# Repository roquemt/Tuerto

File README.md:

# Tuerto
Obstacle avoider robot controled with a FSM 

Top view

Bottom view

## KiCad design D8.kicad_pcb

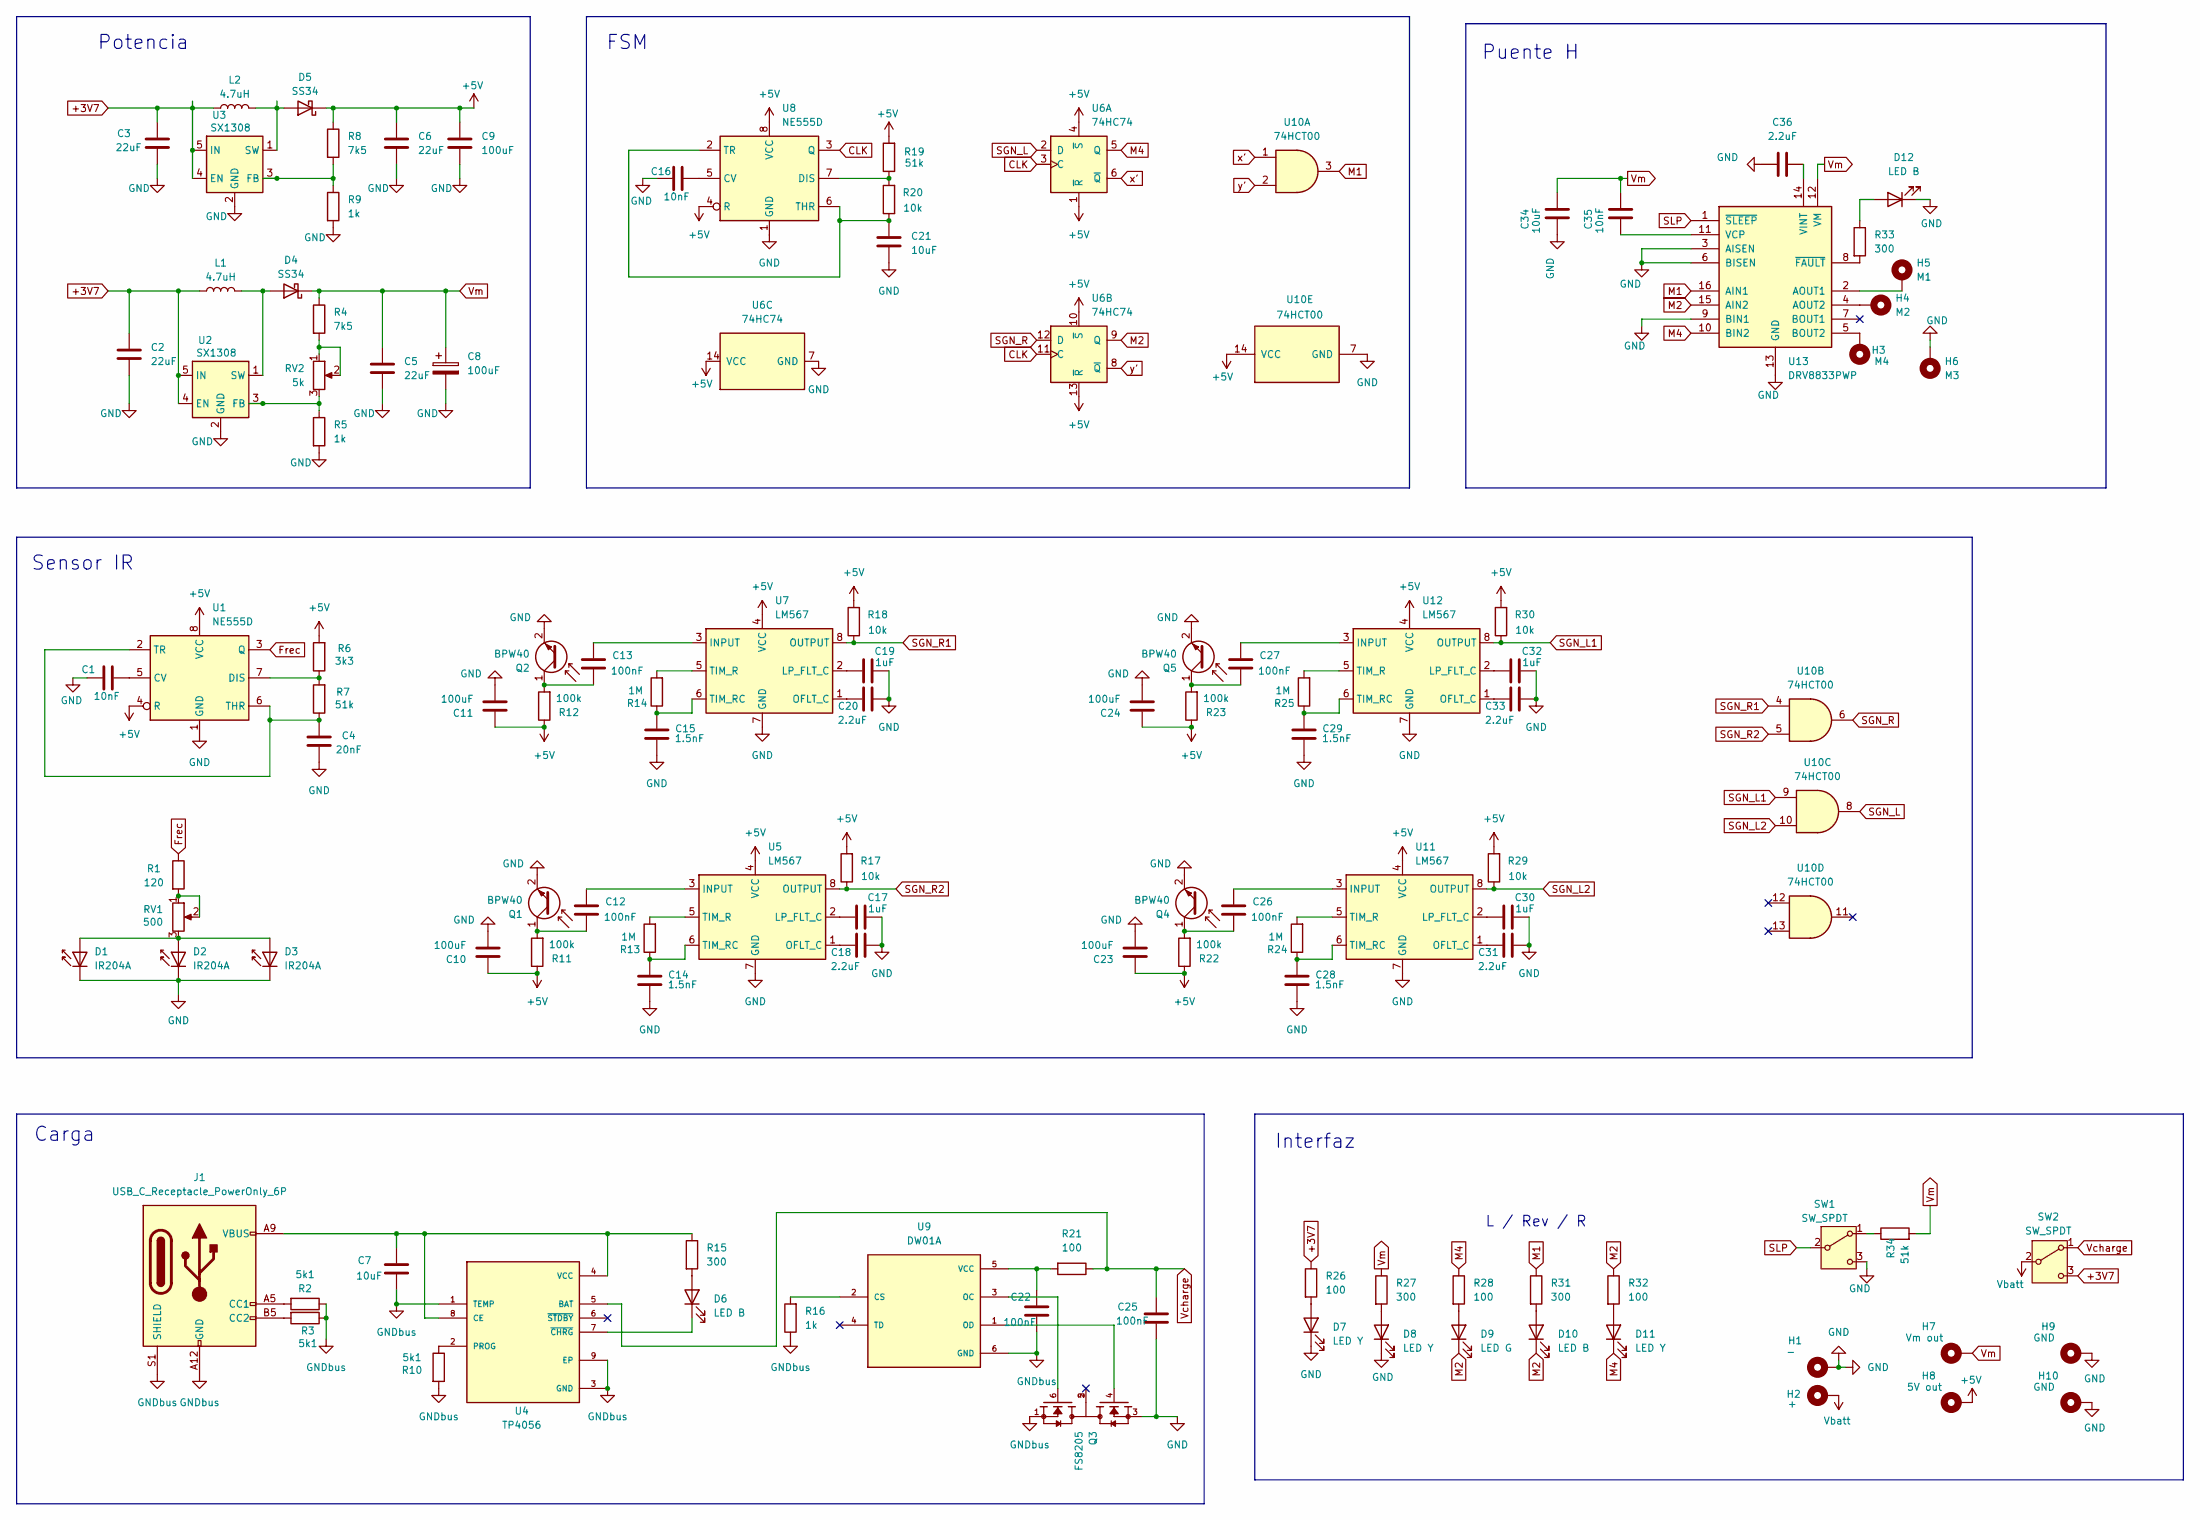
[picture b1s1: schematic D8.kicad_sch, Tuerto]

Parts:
C1, C16, C35: 10nF; C_0603_1608Metric
C2, C3, C5, C6: 22uF; C_0805_2012Metric
C4: 20nF; C_0603_1608Metric
C7, C21, C34: 10uF; C_0603_1608Metric
C8: 100uF; CP_EIA-6032-20_AVX-F_Pad2.25x2.35mm_HandSolder; Manufacturer Part Number TAJD107K016RNJ
C9, C10, C11, C23, C24: 100uF; C_1206_3216Metric
C12, C13, C22, C25, C26, C27: 100nF; C_0603_1608Metric
C14, C15, C28, C29: 1.5nF; C_0603_1608Metric
C17, C19, C30, C32: 1uF; C_0603_1608Metric
C18, C20, C31, C33, C36: 2.2uF; C_0603_1608Metric
D1, D2, D3: IR204A; LED_D3.0mm_IRBlack
D4, D5: SS34; D_SMA; Manufacturer Part Number SS34
D6, D10, D12: LED B; LED_1206_3216Metric
D7, D8, D11: LED Y; LED_1206_3216Metric
D9: LED G; LED_1206_3216Metric
H1: -; SolderWirePad_1x01_SMD_1x2mm
H2: +; SolderWirePad_1x01_SMD_1x2mm
H3: M4; MountingHole_2.2mm_M2_Pad
H4: M2; MountingHole_2.2mm_M2_Pad
H5: M1; MountingHole_2.2mm_M2_Pad
H6: M3; MountingHole_2.2mm_M2_Pad
H7: Vm out; SolderWirePad_1x01_SMD_1x2mm
H8: 5V out; SolderWirePad_1x01_SMD_1x2mm
H9, H10: GND; SolderWirePad_1x01_SMD_1x2mm
J1: USB_C_Receptacle_PowerOnly_6P; USB_C_Receptacle_GCT_USB4125-xx-x-0190_6P_TopMnt_Horizontal
L1, L2: 4.7uH; L_Changjiang_FNR4018S; Manufacturer Part Number FNR4018S4R7MT
Q1, Q2, Q4, Q5: BPW40; LED_D5.0mm_Clear
Q3: FS8205; SOT-23-6; Manufacturer Part Number FS8205A
R1: 120; R_1206_3216Metric
R2, R3, R10: 5k1; R_0603_1608Metric
R4: 7k5; R_0603_1608Metric
R5, R9, R16: 1k; R_0603_1608Metric
R6: 3k3; R_0603_1608Metric
R7, R19, R34: 51k; R_0603_1608Metric
R8: 7k5; R_0603_1608Metric; Manufacturer Part Number 0603WAF7501T5E
R11, R12, R22, R23: 100k; R_0603_1608Metric
R13, R14, R24, R25: 1M; R_0603_1608Metric
R15, R27, R31, R33: 300; R_1206_3216Metric
R17, R18, R20, R29, R30: 10k; R_0603_1608Metric
R21: 100; R_0603_1608Metric
R26, R28, R32: 100; R_1206_3216Metric
RV1: 500; Potentiometer_Bourns_TC33X_Vertical; Manufacturer Part Number TC33X-2-103E
RV2: 5k; Potentiometer_Bourns_TC33X_Vertical; Manufacturer Part Number TC33X-2-103E
SW1, SW2: SW_SPDT; SW_SPDT_PCM12; Manufacturer Part Number SK-3296S-01-L1
U1, U8: NE555D; SOIC-8_3.9x4.9mm_P1.27mm; Manufacturer Part Number NE555D
U2, U3: SX1308; SOT-23-6; Manufacturer Part Number SX1308
U4: TP4056; SOP-8-1EP_4.57x4.57mm_P1.27mm_EP4.57x4.45mm; Manufacturer Part Number TP4056
U5, U7, U11, U12: LM567; SOP-8_3.9x4.9mm_P1.27mm
U6: 74HC74; TSSOP-14_4.4x5mm_P0.65mm; Manufacturer Part Number SN74HCT74PWR
U9: DW01A; SOT-23-6; Manufacturer Part Number DW01
U10: 74HCT00; TSSOP-14_4.4x5mm_P0.65mm
U13: DRV8833PWP; HTSSOP-16-1EP_4.4x5mm_P0.65mm_EP3.4x5mm_Mask2.46x2.31mm; Manufacturer Part Number DRV8833PWPR

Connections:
+3V7: C2.1, C3.1, L1.1, L2.1, R26.1, SW2.3 (C), U2.4 (EN), U2.5 (IN), U3.4 (EN), U3.5 (IN)
+5V: C6.1, C9.1, C10.2, C11.2, C23.2, C24.2, D5.1 (K), H8.1, R6.2, R8.1, R11.1, R12.1, R17.2, R18.2, R19.2, R22.1, R23.1, R29.2, R30.2, U1.4 (R), U1.8 (VCC), U5.4 (VCC), U6.1 (~R), U6.4 (~S), U6.10 (~S), U6.13 (~R), U6.14 (VCC), U7.4 (VCC), U8.4 (R), U8.8 (VCC), U10.14 (VCC), U11.4 (VCC), U12.4 (VCC)
CLK: U6.3 (C), U6.11 (C), U8.3 (Q)
Frec: R1.1, U1.3 (Q)
GND: C1.1, C2.2, C3.2, C4.1, C5.2, C6.2, C8.2, C9.2, C10.1, C11.1, C14.1, C15.1, C16.1, C17.2, C18.2, C19.2, C20.2, C21.1, C23.1, C24.1, C25.2, C28.1, C29.1, C30.2, C31.2, C32.2, C33.2, C34.2, C36.1, D1.1 (K), D2.1 (K), D3.1 (K), D7.1 (K), D8.1 (K), D12.1 (K), H1.1, H6.1, H9.1, H10.1, Q1.2 (E), Q2.2 (E), Q3.3, Q4.2 (E), Q5.2 (E), R5.2, R9.2, SW1.3 (C), U1.1 (GND), U2.2 (GND), U3.2 (GND), U5.7 (GND), U6.7 (GND), U7.7 (GND), U8.1 (GND), U10.7 (GND), U11.7 (GND), U12.7 (GND), U13.3 (AISEN), U13.6 (BISEN), U13.9 (BIN1), U13.13 (GND), U13.17 (GND)
GNDbus: C7.2, C22.2, J1.A12 (GND), J1.B12 (GND), J1.S1 (SHIELD), Q3.1, R2.1, R3.1, R10.2, R16.1, U4.1 (TEMP), U4.3 (GND), U4.9 (EP), U9.6 (GND)
M1: R31.1, U10.3, U13.16 (AIN1)
M2: D9.1 (K), D10.1 (K), R32.1, U6.9 (Q), U13.15 (AIN2)
M4: D11.1 (K), R28.1, U6.5 (Q), U13.10 (BIN2)
unnamed: D1.2 (A), D2.2 (A), D3.2 (A), RV1.3
unnamed: D4.2 (A), L1.2, U2.1 (SW)
unnamed: D5.2 (A), L2.2, U3.1 (SW)
unnamed: D6.2 (A), R15.2
unnamed: D6.1 (K), U4.7 (~CHRG)
unnamed: D7.2 (A), R26.2
unnamed: D8.2 (A), R27.2
unnamed: D9.2 (A), R28.2
unnamed: D10.2 (A), R31.2
unnamed: D11.2 (A), R32.2
unnamed: D12.2 (A), R33.1
unnamed: J1.A5 (CC1), R2.2
unnamed: J1.B5 (CC2), R3.2
unnamed: C12.2, Q1.1 (C), R11.2
unnamed: C13.2, Q2.1 (C), R12.2
unnamed: C26.2, Q4.1 (C), R22.2
unnamed: C27.2, Q5.1 (C), R23.2
unnamed: R1.2, RV1.1, RV1.2
unnamed: R4.2, RV2.1, RV2.2
unnamed: R34.1, SW1.1 (A)
unnamed: C1.2, U1.5 (CV)
unnamed: R6.1, R7.2, U1.7 (DIS)
unnamed: C4.2, R7.1, U1.2 (TR), U1.6 (THR)
unnamed: R5.1, RV2.3, U2.3 (FB)
unnamed: R8.2, R9.1, U3.3 (FB)
unnamed: C7.1, J1.A9 (VBUS), J1.B9 (VBUS), R15.1, U4.4 (VCC), U4.8 (CE)
unnamed: R10.1, U4.2 (PROG)
unnamed: C12.1, U5.3 (INPUT)
unnamed: C17.1, U5.2 (LP_FLT_C)
unnamed: C18.1, U5.1 (OFLT_C)
unnamed: R13.2, U5.5 (TIM_R)
unnamed: C14.2, R13.1, U5.6 (TIM_RC)
unnamed: C13.1, U7.3 (INPUT)
unnamed: C19.1, U7.2 (LP_FLT_C)
unnamed: C20.1, U7.1 (OFLT_C)
unnamed: R14.2, U7.5 (TIM_R)
unnamed: C15.2, R14.1, U7.6 (TIM_RC)
unnamed: C16.2, U8.5 (CV)
unnamed: R19.1, R20.2, U8.7 (DIS)
unnamed: C21.2, R20.1, U8.2 (TR), U8.6 (THR)
unnamed: R16.2, U9.2 (CS)
unnamed: Q3.6, U9.3 (OC)
unnamed: Q3.4, U9.1 (OD)
unnamed: C22.1, R21.2, U9.5 (VCC)
unnamed: C26.1, U11.3 (INPUT)
unnamed: C30.1, U11.2 (LP_FLT_C)
unnamed: C31.1, U11.1 (OFLT_C)
unnamed: R24.2, U11.5 (TIM_R)
unnamed: C28.2, R24.1, U11.6 (TIM_RC)
unnamed: C27.1, U12.3 (INPUT)
unnamed: C32.1, U12.2 (LP_FLT_C)
unnamed: C33.1, U12.1 (OFLT_C)
unnamed: R25.2, U12.5 (TIM_R)
unnamed: C29.2, R25.1, U12.6 (TIM_RC)
unnamed: H5.1, U13.2 (AOUT1)
unnamed: H4.1, U13.4 (AOUT2)
unnamed: H3.1, U13.5 (BOUT2)
unnamed: C35.2, U13.11 (VCP)
unnamed: C36.2, U13.14 (VINT)
unnamed: R33.2, U13.8 (~FAULT)
SGN_L: U6.2 (D), U10.8
SGN_L1: R30.1, U10.9, U12.8 (OUTPUT)
SGN_L2: R29.1, U10.10, U11.8 (OUTPUT)
SGN_R: U6.12 (D), U10.6
SGN_R1: R18.1, U7.8 (OUTPUT), U10.4
SGN_R2: R17.1, U5.8 (OUTPUT), U10.5
SLP: SW1.2 (B), U13.1 (~SLEEP)
Vbatt: H2.1, SW2.2 (B)
Vcharge: C25.1, R21.1, SW2.1 (A), U4.5 (BAT)
Vm: C5.1, C8.1, C34.1, C35.1, D4.1 (K), H7.1, R4.1, R27.1, R34.2, U13.12 (VM)
x': U6.6 (~Q), U10.1
y': U6.8 (~Q), U10.2

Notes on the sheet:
Carga
Interfaz
Sensor IR
Puente H
FSM
L / Rev / R
Potencia

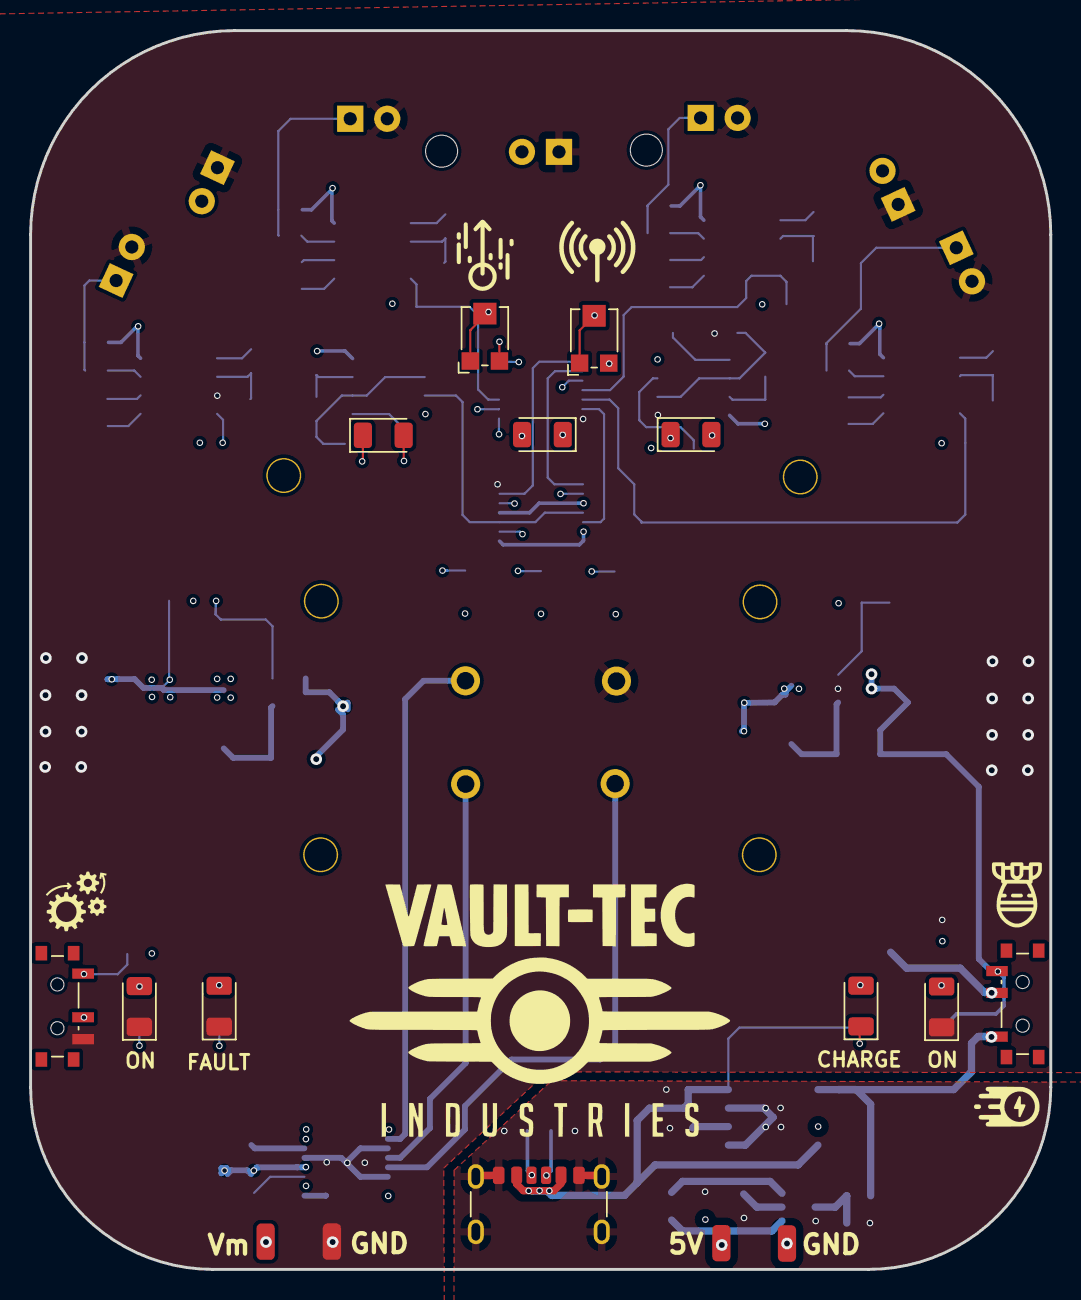
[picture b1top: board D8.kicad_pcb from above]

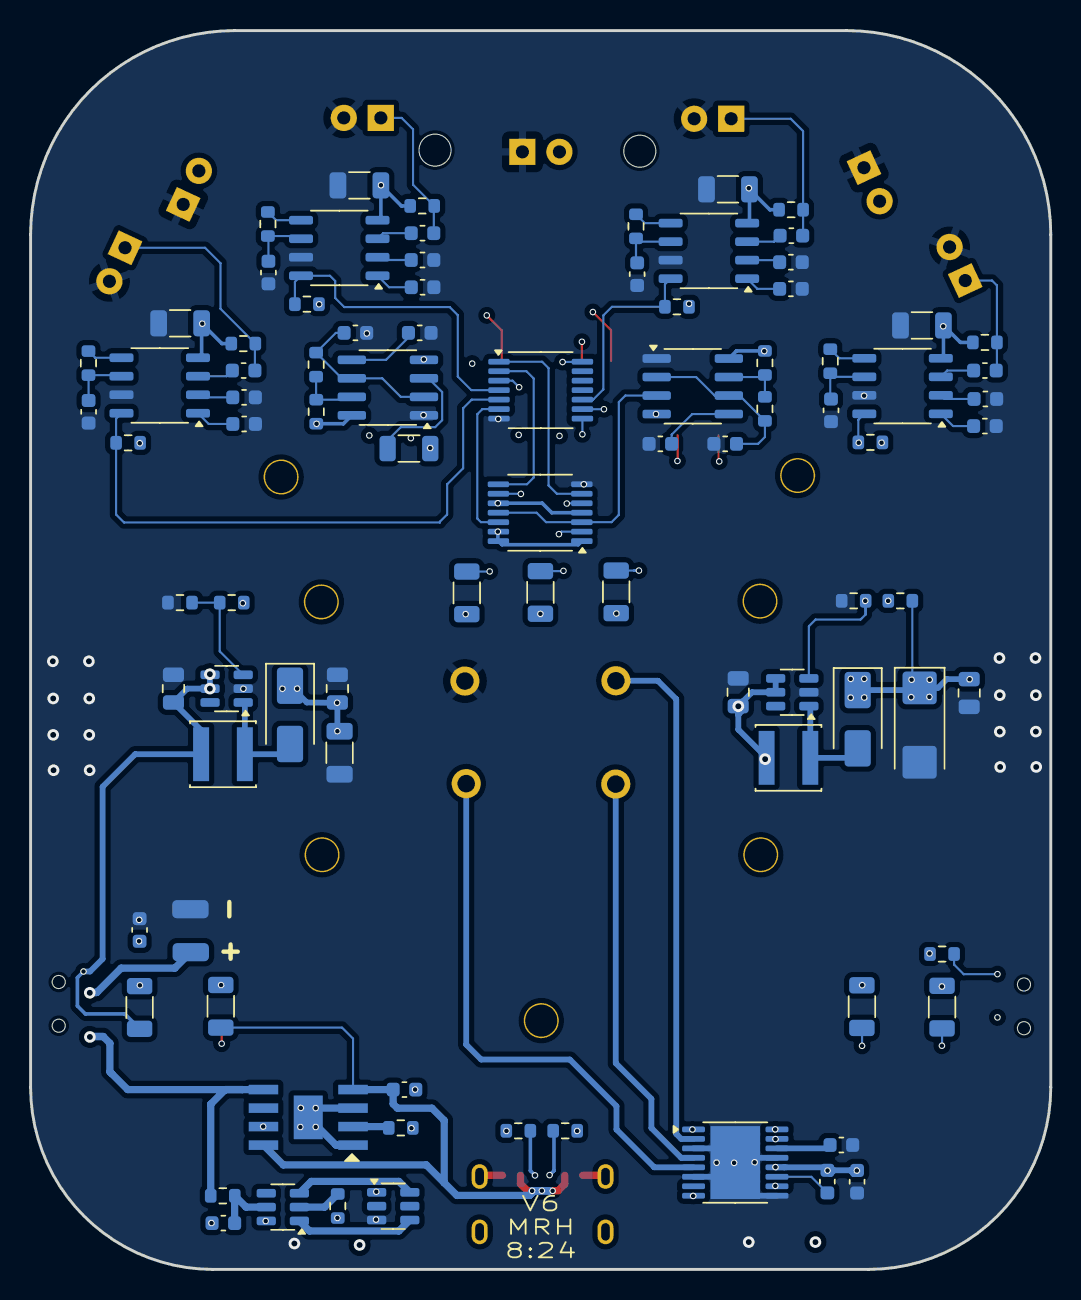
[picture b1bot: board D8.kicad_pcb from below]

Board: 4 copper layers, 70.0 x 85.0 mm, 117 parts (90 on the bottom side), 81 nets.
